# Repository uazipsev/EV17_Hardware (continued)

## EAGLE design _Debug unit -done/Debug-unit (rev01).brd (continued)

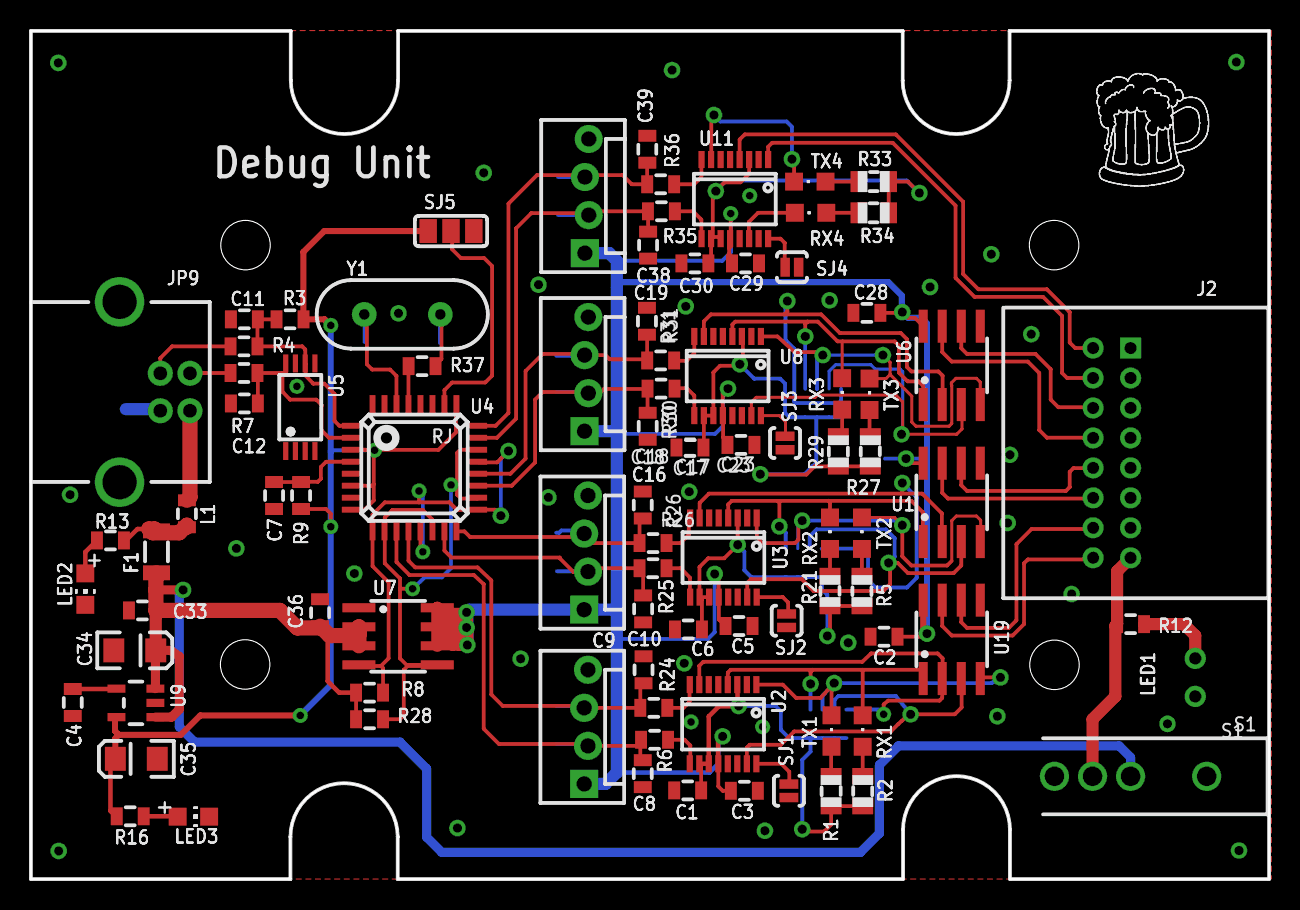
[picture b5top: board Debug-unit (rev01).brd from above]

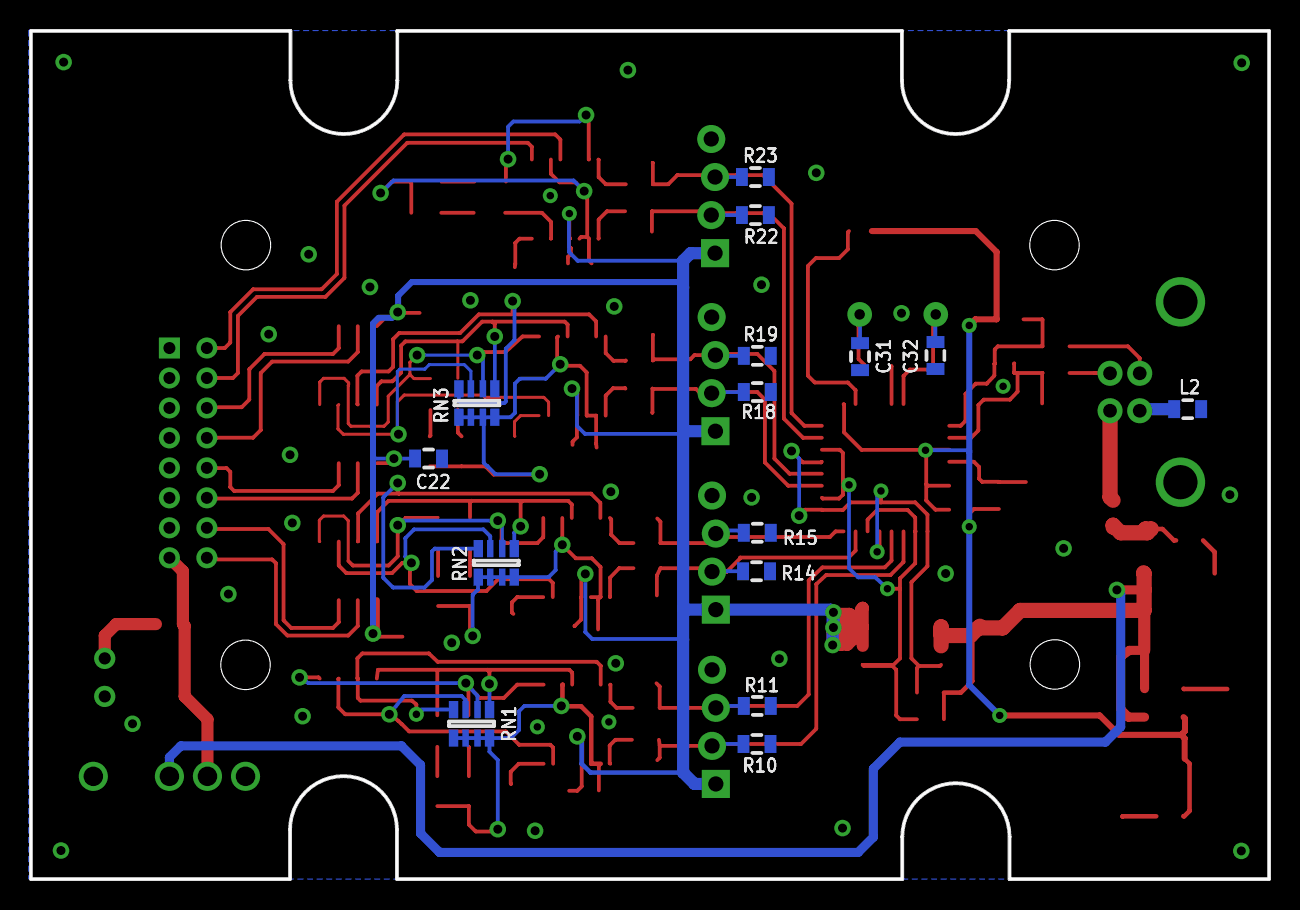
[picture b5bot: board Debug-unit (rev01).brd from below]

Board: 2 copper layers, 82.7 x 56.6 mm, 106 parts (15 on the bottom side), 77 nets.

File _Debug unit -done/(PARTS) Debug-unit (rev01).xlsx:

type | qty | Part | Value | Package | Note
 | 8 | R6, 24, 26, 27, 31, 32, 35, 36 | 27 | R0805 | 0.01
 | 12 | C1, 2, 3, 5, 6, 22, 23, 24, 28, 29, 30, 33 | 0.1uF | 805
 | 1 | R3, R37 | 1.5k | R0805 | 0.01
 | 1 | R28 | 10k | R0805
 | 8 | R10, 11, 14, 15, 18, 19, 22, 23 | 15k | R0805
 | 8 | R1, 2, 5, 25, 29, 30, 33, 34 | 1K | R0805
 | 1 | C36 | 1uF | 805
 | 2 | C34, 35 | 4.7uF | CAP_POL1206/EIA3216
 | 8 | C8, 9, 10, 21, 26, 27, 38, 39 | 47pf | 805
 | 1 | Y1 | HC-49/U-S6000000ABJB
 | 4 | U2, 3, 8, 11 | FT230X | SSOP-16
 | 1 | U9 | V_REG_MIC5219 3.3V | SOT23-5
 | 3 | RN1, 2, 3 | RN-4 | CRA06S
 | 1 | U5 | SN75240PWR | TSSOP-8
 | 3 | U1, 6, 19 | SN75HVD08D | SO-8
 | 1 | U7 | TPS2041BDR | SO-8
 | 1 | U4 | TUSB2046BI VFR | LQFP-32
 | 1 | JP9 | USB-B | USB-B-PTH | USB Connection Molex 4 pin
con | 4 | JP1, 2, 3, 4 |  | MOLEX-1X4_LOCK | Need matching part
LED |  | RX1, 2, 3, 4 | Red | CHIPLED_0805 | color
switch |  | S1 |  | SWITCH-SPDT
LED | 4 | TX1, TX2, TX3, TX4 | Green | CHIPLED_0805

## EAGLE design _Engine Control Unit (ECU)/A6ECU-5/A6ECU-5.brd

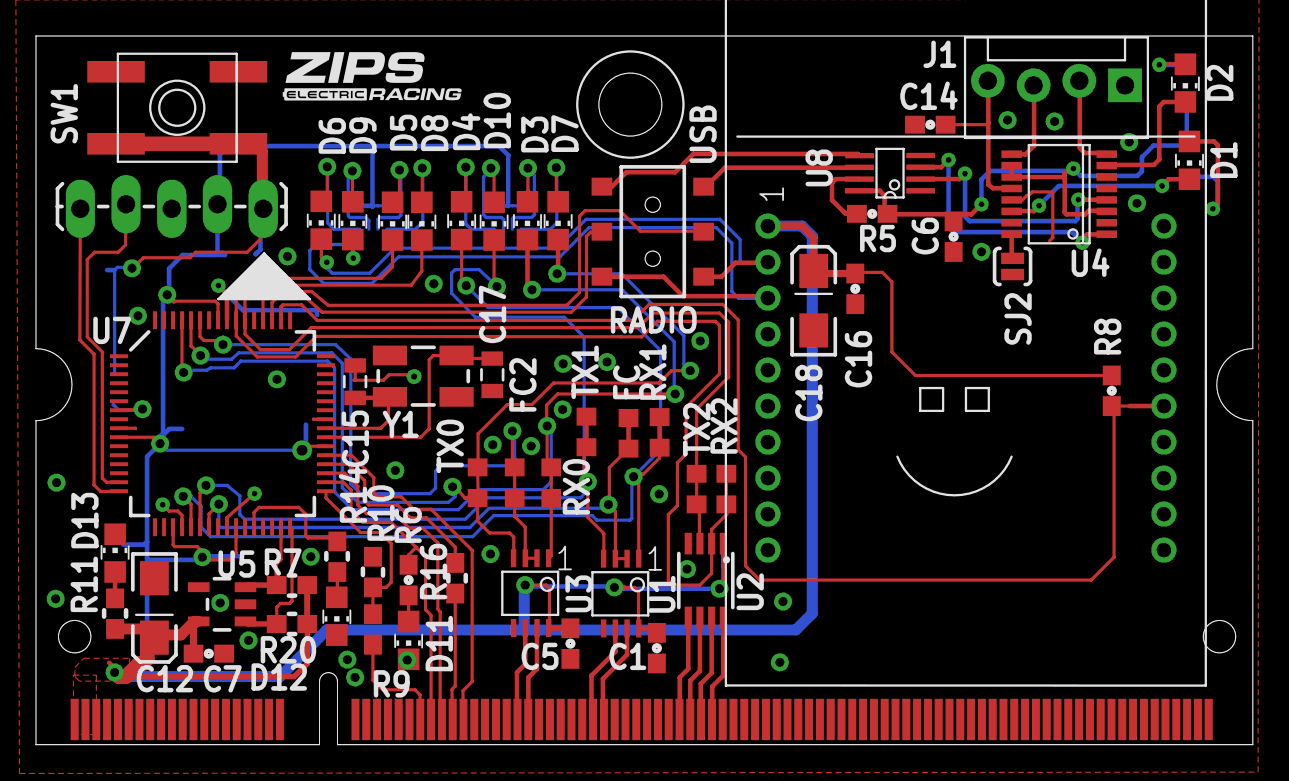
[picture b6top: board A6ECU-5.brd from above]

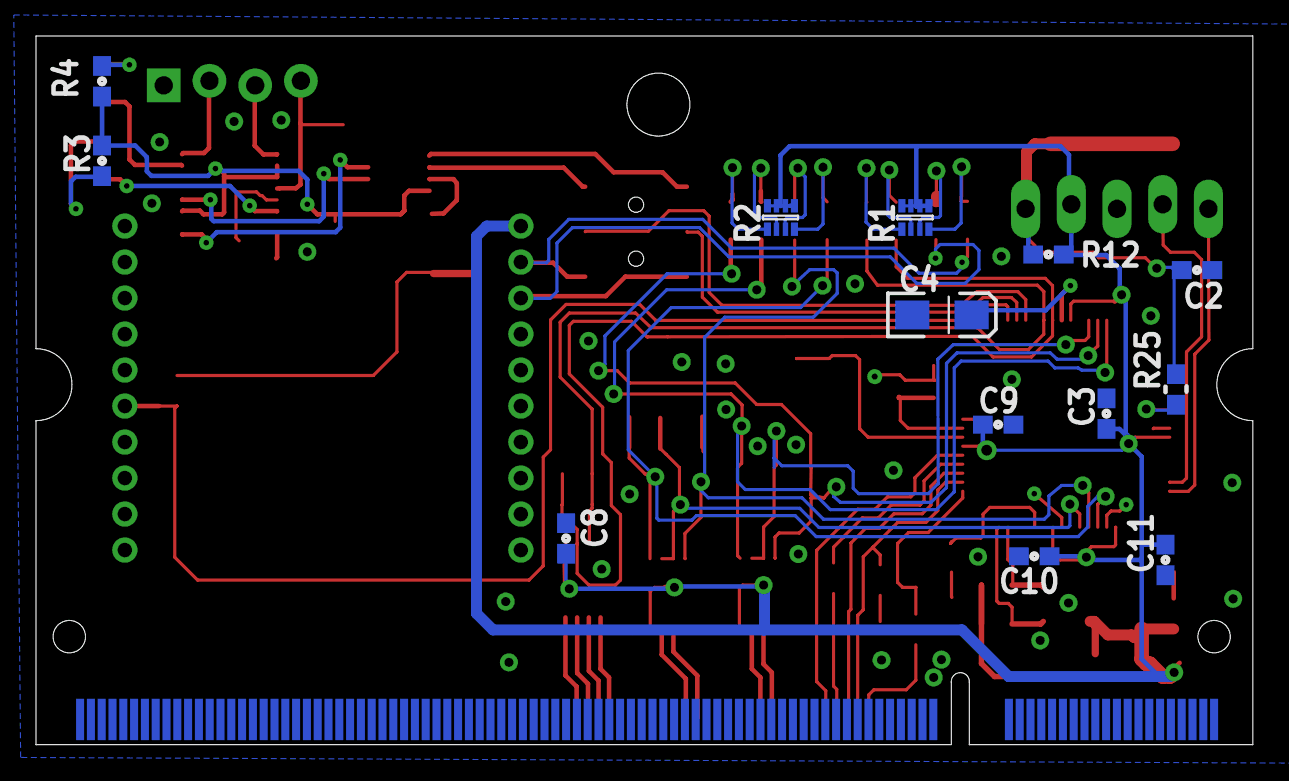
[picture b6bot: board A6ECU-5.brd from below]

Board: 2 copper layers, 67.6 x 39.4 mm, 71 parts (13 on the bottom side), 65 nets.

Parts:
C1, C2, C3, C5, C6, C7, C8, C9, C10, C11, C14, C16: 0.1UF; 0603
C4, C12, C18: 10UF; EIA3216-16V
C15, C17: 12PF; 0805
D1, D3, D4, D5, D6: RED; CHIP_LED0805
D2, D7, D8, D9, D10, D13: GREEN; CHIP_LED0805
D11: ORANGE; CHIP_LED0805
D12: AMBER; CHIP_LED0805
FC, FC2: TESTPOINT; R0603
ICSP: ICSP; 1X05_LOCK_LONGPADS
J1: M4_1X4_LOCK; MOLEX_1X4
R1, R2: RN-4_1K; MNR14
R3, R4, R5, R6, R8: 1K; 0603
R7, R20: 2k; 0603
R9: 30k; 0603
R10: 10k; 0603
R11, R14, R25: 499; 0603
R12: 10K; 0603
R16: 1k; 0603
RX0, RX1, RX2: TESTPOINT; R0603
S1: DPDT; AYZ0202
SJ2: PAD-JUMPER-2-NO_YES_SILK
SW1: SPST_TACT-EVQQ2; EVQ-Q2
TX0, TX1, TX2: TESTPOINT; R0603
U1, U3: SN75HVD08DRMSOP; MSOP-8
U2: ISL83077MSOP; MSOP8
U4: FT230X; SSOP-16
U5: 24LC00T-I/OT; SOT23-5
U6: RM024; RM024-TH
U7: DSPIC33EP256GM306; TQFP-64
U8: SN74LVC2G241; VFSOP-8
U$1: INDPK1; PICKIT-PIN-1
U$2: LOGO16-2-M; 2016-2-LOGO-M
X1: 1376408-SLOT_1.8V; SLOT-1376408-1_1.8V
Y1: 12Mhz; CRYSTAL-SMD-5X3

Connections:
3V: C6.1, R3.2, R4.2, R5.2, U4.3, U4.10, U4.11, U8.8
+3V3: C1.1, C3.1, C5.1, C7.1, C8.1, C9.1, C10.1, C11.2, C12.A, C16.1, C18.A, ICSP.2, R1.5, R1.6, R1.7, R1.8, R2.5, R2.6, R2.7, R2.8, R7.2, R8.2, R11.2, R12.2, R20.2, U1.8, U2.1, U3.8, U5.5, U6.1, U7.10, U7.19, U7.26, U7.38, U7.57, X1.1, X1.3, X1.5
BRAKELIGHT: U7.35, X1.57
ECU-SS-IN: R9.2, X1.53
GND: C1.2, C2.2, C3.2, C4.C, C5.2, C6.2, C7.2, C8.2, C9.2, C10.2, C11.1, C12.C, C14.2, C15.2, C16.2, C17.2, C18.C, D11.C, D12.C, D13.C, ICSP.3, J1.1, R10.1, SJ2.1, SW1.A, SW1.A', U1.5, U2.4, U3.5, U4.5, U4.13, U5.2, U6.10, U7.9, U7.20, U7.25, U7.41, U8.1, U8.4, X1.195, X1.196, X1.197, X1.198, X1.199, X1.200
HORN: R16.1, X1.59
HORNEN: U7.37, X1.61
INRG: R8.1, U6.15, U7.50
unnamed: D7.A, R2.1
unnamed: R14.2, U7.28
unnamed: D13.A, R11.1
unnamed: D2.A, R4.1
unnamed: D3.A, R2.2
unnamed: D4.A, R2.4
unnamed: D10.A, R2.3
unnamed: D8.A, R1.1
unnamed: D5.A, R1.2
unnamed: D6.A, R1.4
unnamed: D9.A, R1.3
unnamed: D11.A, R6.1
unnamed: C15.1, U7.40, Y1.3
unnamed: C17.1, U7.39, Y1.1
unnamed: D12.A, R14.1
unnamed: R7.1, U5.3, U7.31
unnamed: SJ2.2, U4.16
unnamed: D1.A, R3.1
unnamed: D2.C, U4.7
unnamed: D1.C, U4.14
unnamed: U4.4, U8.2
unnamed: C2.1, ICSP.1, R12.1, R25.1, SW1.B, SW1.B'
unnamed: U4.1, U8.3
unnamed: J1.3, U4.9
unnamed: R20.1, U5.1, U7.32
unnamed: J1.2, U4.8
unnamed: R5.1, U8.7
unnamed: C14.1, J1.4, U4.12
unnamed: R25.2, U7.7
unnamed: C4.A, U7.56
unnamed: ICSP.4, U7.15
unnamed: ICSP.5, U7.16
RS485-1-A: U3.6, X1.71
RS485-1-B: U3.7, X1.73
RS485-2-A: U1.6, X1.85
RS485-2-B: U1.7, X1.87
RS-TM-A: U2.8, X1.107
RS-TM-B: U2.7, X1.105
RS-TM-Y: U2.5, X1.101
RS-TM-Z: U2.6, X1.103
RTD-HORN: R16.2, U7.36
RX: S1.2, U7.52
RXD0: D3.C, RX0.1, RX0.2, U3.1, U7.61
RXD1: D4.C, RX1.1, RX1.2, U1.1, U7.21
RXD2: D5.C, RX2.1, RX2.2, U2.2, U7.55
RXD3: S1.1, U8.6
RXD4: D6.C, S1.3, U6.2
SS-D: R9.1, R10.2, U7.33
SS-ECU-RELAY: R6.2, U7.34, X1.55
TX: S1.5, U7.51
TXD0: D7.C, TX0.1, TX0.2, U3.4, U7.60
TXD1: D10.C, TX1.1, TX1.2, U1.4, U7.22
TXD2: D8.C, TX2.1, TX2.2, U2.3, U7.54
TXD3: S1.4, U8.5
TXD4: D9.C, S1.6, U6.3
U1-EN: FC.1, FC.2, U1.2, U1.3, U7.23
U3-EN: FC2.1, FC2.2, U3.2, U3.3, U7.59

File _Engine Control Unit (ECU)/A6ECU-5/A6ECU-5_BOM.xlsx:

Qty-1 | Part References | Value | Package | Mfg Part Num | Mfg Name | VID | Vendor Part Num | Description | Pkg Code | XREF
12 | C1, C2, C3, C5, C6, C7, C8, C9, C10, C11, C14, C16 | 0.1UF | 603 | CC0603ZRY5V9BB104 | Yageo | DK | 311-1343-1-ND | CAP CER 0.1UF 50V Y5V 0603 | 0603 (1608 Metric) | REF13
5 | R3, R4, R5, R6, R8 | 1K | 603 | RC0603JR-071KL | Yageo | DK | 311-1.0KGRCT-ND | RES SMD 1K OHM 5% 1/10W 0603 | 0603 (1608 Metric) | REF84
1 | R16 | 1k | 603 | RC0603JR-071KL | Yageo | DK | 311-1.0KGRCT-ND | RES SMD 1K OHM 5% 1/10W 0603 | 0603 (1608 Metric) | REF84
2 | R7, R20 | 2k | 603 | ERJ-3EKF2001V | Panasonic Electronic Components | DK | P2.00KHCT-ND | RES SMD 2K OHM 1% 1/10W 0603 | 0603 (1608 Metric) | REF91
1 | R12 | 10K | 603 | RC0603FR-0710KL | Yageo | DK | 311-10.0KHRCT-ND | RES SMD 10K OHM 1% 1/10W 0603 | 0603 (1608 Metric) | REF85
3 | C4, C12, C18 | 10UF | EIA3216-16V | T491A106M016AT | Kemet | DK | 399-3687-1-ND | CAP TANT 10UF 16V 20% 1206 | 1206 (3216 Metric) | REF173
1 | R10 | 10k | 603 | RC0603FR-0710KL | Yageo | DK | 311-10.0KHRCT-ND | RES SMD 10K OHM 1% 1/10W 0603 | 0603 (1608 Metric) | REF85
1 | Y1 | 12Mhz | CRYSTAL-SMD-5X3 | ***PART# '*' NOT FOUND*** | * | * | * | * | * | *
2 | C15, C17 | 12PF | 805 | CL21C120JBANNNC | Samsung Electro-Mechanics America | Inc. | DK | 1276-1120-1-ND | CAP CER 12PF 50V NP0 0805 | 0805 (2012 Metric) | REF21
1 | U5 | 24LC00T-I/OT | SOT23-5 | 24LC00T-I/OT | Microchip Technology | DK | 24LC00T-I/OTCT-ND | IC EEPROM 128BIT 400KHZ SOT23-5 | SC-74A | SOT-753 | REF270
1 | R9 | 30k | 603 | RC0603FR-0730KL | Yageo | DK | 311-30.0KHRCT-ND | RES SMD 30K OHM 1% 1/10W 0603 | 0603 (1608 Metric) | REF101
3 | R11, R14, R25 | 499 | 603 | RC0603FR-07499RL | Yageo | DK | 311-499HRCT-ND | RES SMD 499 OHM 1% 1/10W 0603 | 0603 (1608 Metric) | REF86
1 | D12 | AMBER | CHIP_LED0805 | HSMA-C170 | Avago Technologies US Inc. | DK | 516-1431-1-ND | LED AMBER DIFFUSED 0805 SMD | 0805 (2012 Metric) | REF39
1 | S1 | DPDT | AYZ0202 | AYZ0202AGRLC | C&K; Components | DK | 401-2013-1-ND | SWITCH SLIDE DPDT 100MA 12V | None | REF266
1 | U7 | DSPIC33EP256GM306 | TQFP-64 | DSPIC33EP256GM306-I/PT | Microchip Technology | DK | DSPIC33EP256GM306-I/PT-ND | IC DSC 16BIT 256KB FLASH 64TQFP | 64-TQFP | REF48
1 | U4 | FT230X | SSOP-16 | FT230XS-R | FTDI | DK | 768-1135-1-ND | IC USB SERIAL BASIC UART 16SSOP | 16-SSOP (0.154" | 3.90mm Width) | REF46
6 | D2, D7, D8, D9, D10, D13 | GREEN | CHIP_LED0805 | LTST-S220GKT | Lite-On Inc. | DK | 160-1218-1-ND | LED GREEN CLEAR 0805 R/A SMD | 0805 (2012 Metric) | REF35
1 | ICSP | ICSP | 1X05_LOCK_LONGPADS | ***PART# '*' NOT FOUND*** | * | * | * | * | * | *
1 | U2 | ISL83077MSOP | MSOP8 | ISL83072EIUZA-T | Intersil | DK | ISL83072EIUZA-TCT-ND | TXRX ESD RS-485/422 LP 8-MSOP | 8-TSSOP | 8-MSOP (0.118" | 3.00mm Width) | REF57
1 | J1 | M4_1X4_LOCK | MOLEX_1X4 | 22232041 | Molex | LLC | DK | WM4202-ND | CONN HEADER 4POS .100 VERT TIN | None | REF179
1 | D11 | ORANGE | CHIP_LED0805 | LTST-C170KFKT | Lite-On Inc. | DK | 160-1413-1-ND | LED ORANGE CLEAR 0805 SMD | 0805 (2012 Metric) | REF37
5 | D1, D3, D4, D5, D6 | RED | CHIP_LED0805 | LH R974-LP-1 | OSRAM Opto Semiconductors Inc. | DK | 475-1415-1-ND | LED RED DIFFUSED 0805 SMD | 0805 (2012 Metric) | REF36
1 | U6 | RM024 | RM024-TH | ***PART# '*' NOT FOUND*** | * | * | * | * | * | *
2 | R1, R2 | RN-4_1K | MNR14 | MNR14ERAPJ102 | Rohm Semiconductor | DK | RHM1595CT-ND | RES ARRAY 4 RES 1K OHM 1206 | 1206 (3216 Metric) | Convex | Long Side Terminals | REF174
1 | U8 | SN74LVC2G241 | VFSOP-8 | SN74LVC2G241DCUR | Texas Instruments | DK | 296-11936-1-ND | IC BUFF/DVR TRI-ST DL US8 | 8-VFSOP (0.091" | 2.30mm Width) | REF176
2 | U1, U3 | SN75HVD08DRMSOP | MSOP-8 | ISL83072EIUZA-T | Intersil | DK | ISL83072EIUZA-TCT-ND | TXRX ESD RS-485/422 LP 8-MSOP | 8-TSSOP | 8-MSOP (0.118" | 3.00mm Width) | REF57
1 | SW1 | SPST_TACT-EVQQ2 | EVQ-Q2 | EVQ-Q2F03W | Panasonic Electronic Components | DK | P12937SCT-ND | SWITCH TACTILE SPST-NO 0.02A 15V | None | REF268
8 | TX0, FC, FC2, RX0, RX1, RX2, TX1, TX2 | TESTPOINT | R0603 | 1625854-3 | TE Connectivity AMP Connectors | DK | A106145CT-ND | 0603 PROBE PAD | None | REF267
